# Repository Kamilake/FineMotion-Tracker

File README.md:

# SlimeVR Based Full-Body Tracker

```
혹시 트래커를 어디선가 구해서 QR코드를 스캔해 여기에 왔고 구매자가 아무것도 알려주지 않았다면 디스코드 kamilake 로 디엠주세요!
```

ESP8266 Motion Capture Devices for SlimeVR Ecosystem

Thinnest SlimeVR Tracker!

Full SMT PCB operating in MPU-6500 6DoF mode

Operate with all 5V chargers, including C to C PD chargers.

You can use it simply by ordering it from the fabricator

<!--

-->

## Why should that tracker be able to be detached from the strap?

It is because of the start-up calibration of the MPU-6000 series.

When the MPU first powers up, the DMP measures the static noise, but this needs to be done on every boot. In other words, to reboot the tracker in-game, you must detach it from your body. Not only does this strap adapter help make it very convenient, but it is also a great help in tracker maintenance!

It only takes 10 seconds for you to assemble the tracker sensor and adapter, and less than 30 seconds to assemble all the trackers to your body \:P

It is eco-friendly to save the life of Velcro straps and easily replace broken adapters.

## Specification

- Power Rating: 500mA@5V (TProg: 2.4KOhm)
- Wi-Fi: 802.11bgn 2.4GHz (20.5mW@2dBi)
- Protection Circuit: Depend on battery
- IMU: Invensense MPU-6500 6DoF Attitude detection sensor
- The radio wave safety of this product has been verified by a nationally recognized testing agency.

## Prerequirements

- PCB: [This Repo!](/PCBs)
- 3D Model: [This Repo!](/3D%20Models)
- Belt Strap: https://aliexpress.com/item/1005003002833146.html, or any 50mm width Strap
- Battery: https://aliexpress.com/item/1005004165245143.html, or any 702050 Cell
- USB Cable: https://aliexpress.com/item/1005004409330904.html, or any Type-C cables

## How do I make it?

1. [Order PCB!](/PCBs)
2. Order Belt, Battery!
3. [Print Shell!](/3D%20Models)
4. Go to SteamVR...

## defines.h
```cpp
#define FineMotion_v5
#define IMU IMU_MPU6500
#define IMU_ROTATION DEG_0
#define BOARD BOARD_NODEMCU
#define SECOND_IMU IMU
#define SECOND_IMU_ROTATION IMU_ROTATION
#define BATTERY_MONITOR 1
#define BATTERY_SHIELD_RESISTANCE 0
#define BATTERY_SHIELD_R1 12
#define BATTERY_SHIELD_R2 47
#define PIN_IMU_SDA 4
#define PIN_IMU_SCL 5
#define PIN_IMU_INT 0xFF
#define PIN_IMU_INT_2 0xFF
#define PIN_BATTERY_LEVEL 17
```

## Why do trackers have to be thin?

The thinner the tracker, the closer the IMU is to the bone and the better the tracking accuracy. It is less affected by inertial force in fast movements.. Above all, it is comfortable when lying on the bed facing the tracker!

## License
**This hardware is licensed under the CERN-OHL-P v2 license**, which is a permissive,
non-viral and non-reciprocal open hardware license. Unlike software licenses like
MIT and Apache 2.0, it better handles the nuances of hardware and protects both
the licensor and licensee from patent lawsuits.

**Unless you explicitly state otherwise, any contribution intentionally submitted
for inclusion in this work by you, shall be licensed as above, without any
additional terms or conditions.**

### Conveying notice of License
Note that as part of the CERN-OHL-P v2 license, recipients of manufactured
hardware must also receive notice of the above license. One such
method of conveying the notice is to include a link to the original source repo,
or printing "Licensed under CERN-OHL-P v2" on the PCB silkscreen. For more info,
see [here](https://ohwr.org/project/cernohl/wikis/Documents/CERN-OHL-version-2).

This is conceptually similar to the MIT/Apache 2.0 Licenses, where the original
license must still be included as a notice even when the source is modified and
subsequently relicensed under different terms.

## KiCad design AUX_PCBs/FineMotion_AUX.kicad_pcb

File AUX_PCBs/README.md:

# Custom assembly using Kikit JLC

Due to JLCPCB's new assembly policy, soldering on the bottom side or using a non-black PCB will incur additional charges.
Bottom side soldering is not possible if the "Economic" assembly option is selected.
As the bottom side soldering is only for the connector, manual assembly is recommended.  
But.. if you ordering more than 31 boards, it is more economical to choose the `Standard assembly` option with panelization.  
If you have any further questions, please feel free to contact me!(Issues, mail, Discord, etc.)  

- You need `KiCad 6.0 Command Prompt` and [Kikit](https://github.com/yaqwsx/KiKit) with KiCad 6

## Panalize and Fabrication

```batch
kikit panelize ^
    -p :jlcTooling ^
    --layout "grid; rows: 7; cols: 3; space: 3mm" ^
    --tabs "fixed; hwidth: 10mm; vwidth: 15mm" ^
    --cuts vcuts ^
    --source "tolerance: 1000mm" ^
    --framing "tightframe; width: 5mm; space: 3mm; " ^
    --post "millradius: 1mm" ^
    "./FineMotion_AUX.kicad_pcb" ^
    "FineMotion_AUX_panel.kicad_pcb"

kikit fab jlcpcb ^
    --assembly ^
    --schematic ./FineMotion_AUX.kicad_sch ^
    --ignore TP1,J1 ^
    "./FineMotion_AUX_panel.kicad_pcb" ^
    "./Gerber/FineMotion_Panel"

```

## Fabrication Only

### Using Default Configuration

```batch
kikit fab jlcpcb ^
    --assembly ^
    --schematic ./FineMotion_AUX.kicad_sch ^
    --ignore TP1,TP2 ^
    --no-drc ^
    "./FineMotion_AUX_panel.kicad_pcb" ^
    "./Gerber/FineMotion"
```

<br><hr><br>

## Panalize and Fabrication Extension Sensor

```batch
```

## Fabrication Extension Sensor Only

### Using Default Configuration

```batch
```

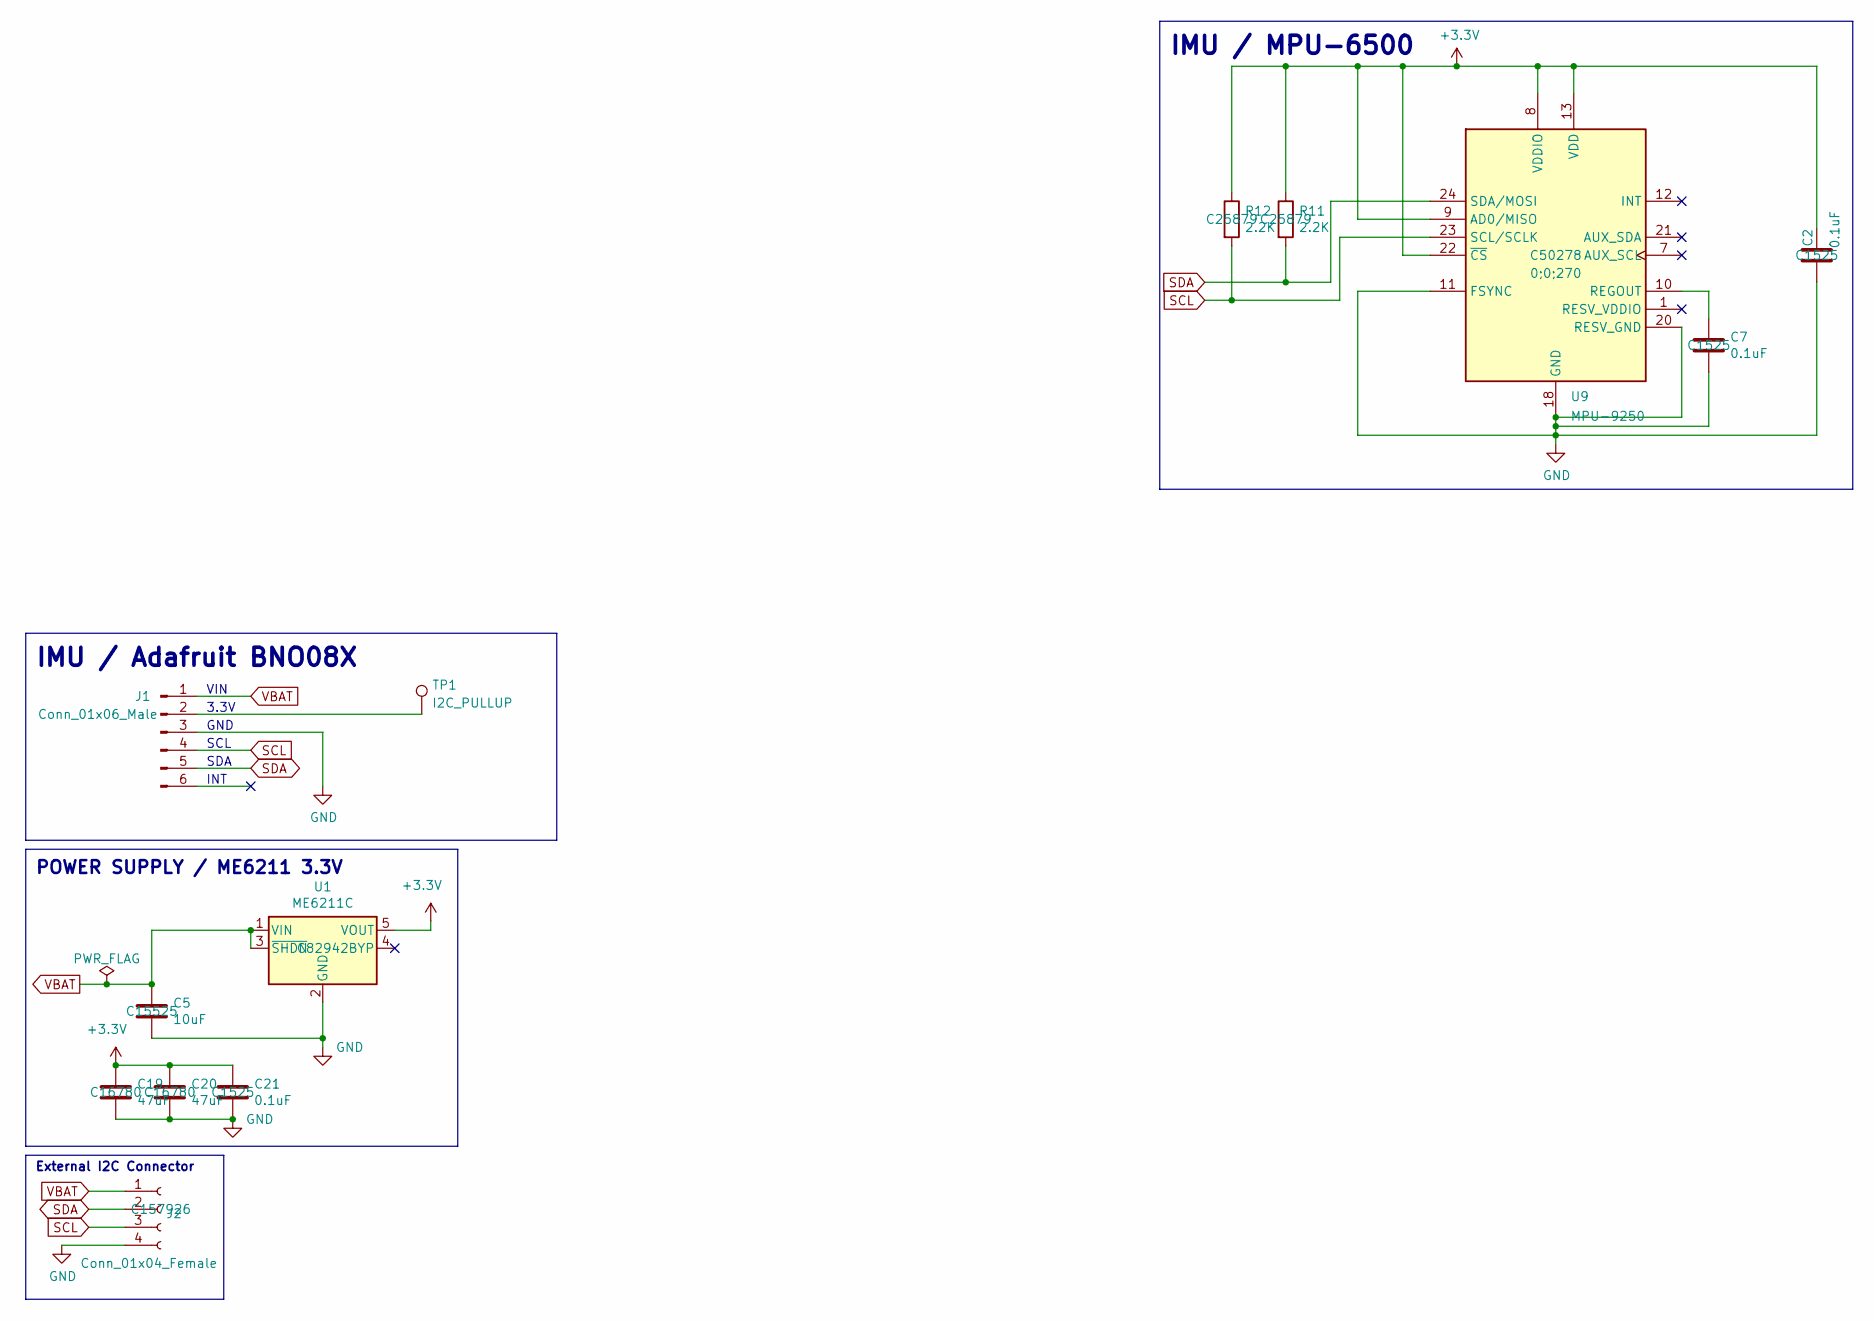
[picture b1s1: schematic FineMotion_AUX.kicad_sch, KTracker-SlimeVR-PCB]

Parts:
C2, C7, C21: 0.1uF; C_0402_1005Metric; LCSC C1525
C5: 10uF; C_0402_1005Metric; LCSC C15525
C19, C20: 47uF; C_0805_2012Metric; LCSC C16780
J1: Conn_01x06_Male; PinHeader_1x06_P2.54mm_Vertical
J2: Conn_01x04_Female; JST_PH_S4B-PH-K_1x04_P2.00mm_Horizontal; LCSC C157926
R11, R12: 2.2K; R_0402_1005Metric; LCSC C25879
TP1: I2C_PULLUP; TestPoint_Pad_D1.5mm
U1: ME6211C; SOT-23-5; LCSC C82942
U9: MPU-9250; InvenSense_QFN-24_3x3mm_P0.4mm; LCSC C50278

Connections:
+3V3: C2.2, C19.1, C20.1, C21.1, R11.1, R12.1, U1.5 (VOUT), U9.8 (VDDIO), U9.9 (AD0/MISO), U9.13 (VDD), U9.22 (~CS)
GND: C2.1, C5.2, C7.2, C19.2, C20.2, C21.2, J1.3, J2.4, U1.2 (GND), U9.11 (FSYNC), U9.18 (GND), U9.20 (RESV_GND)
unnamed: C7.1, U9.10 (REGOUT)
unnamed: J1.2, TP1.1
SCL: J1.4, J2.3, R12.2, U9.23 (SCL/SCLK)
SDA: J1.5, J2.2, R11.2, U9.24 (SDA/MOSI)
VBAT: C5.1, J1.1, J2.1, U1.1 (VIN), U1.3 (~SHDN)

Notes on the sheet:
External I2C Connector
SCL
IMU / MPU-6500
SDA
IMU / Adafruit BNO08X
POWER SUPPLY / ME6211 3.3V
GND
VIN
INT
3.3V

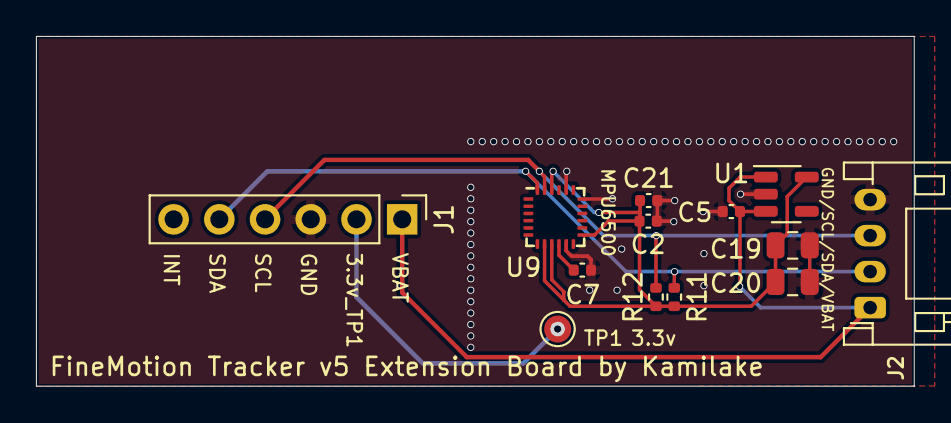
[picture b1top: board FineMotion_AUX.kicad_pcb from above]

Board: 2 copper layers, 48.8 x 19.4 mm, 13 parts (0 on the bottom side), 7 nets.

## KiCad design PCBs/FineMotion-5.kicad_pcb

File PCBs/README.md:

# Custom assembly using Kikit JLC

Due to JLCPCB's new assembly policy, soldering on the bottom side or using a non-black PCB will incur additional charges.   
Bottom side soldering is not possible if the "Economic" assembly option is selected.   
As the bottom side soldering is only for the connector, manual assembly is recommended.  
But.. if you ordering more than 31 boards, it is more economical to choose the `Standard assembly` option with panelization.  
If you have any further questions, please feel free to contact me!(Issues, mail, Discord, etc.)  

- You need `KiCad 6.0 Command Prompt` and [Kikit](https://github.com/yaqwsx/KiKit) with KiCad 6

## Panalize and Fabrication
```batch
kikit panelize ^
    -p :jlcTooling ^
    --layout "grid; rows: 7; cols: 3; space: 3mm" ^
    --tabs "fixed; hwidth: 10mm; vwidth: 15mm" ^
    --cuts vcuts ^
    --source "tolerance: 1000mm" ^
    --post "millradius: 1mm" ^
    "./FineMotion-5.kicad_pcb" ^
    "FineMotion-5_panel.kicad_pcb"

kikit fab jlcpcb ^
    --assembly ^
    --schematic ./FineMotion-5.kicad_sch ^
    --ignore TP1,TP2 ^
    --no-drc ^
    "./FineMotion-5_panel.kicad_pcb" ^
    "./Gerber/FineMotion_Panel"
```

## Fabrication Only

### Using Default Configuration
```batch
kikit fab jlcpcb ^
    --assembly ^
    --schematic ./FineMotion-5.kicad_sch ^
    --ignore TP1,TP2 ^
    --no-drc ^
    "./FineMotion-5_panel.kicad_pcb" ^
    "./Gerber/FineMotion"
```

<br><hr><br>   

## Panalize and Fabrication Extension Sensor
```batch
```

## Fabrication Extension Sensor Only

### Using Default Configuration
```batch
```
<!--
### Using internal MPU-6050+QMC5883L and Left side Lipo
```batch
kikit fab jlcpcb ^
    --assembly ^
    --schematic ./KTracker.kicad_sch ^
    --ignore BT1,J1,J4,J5 ^
    --no-drc ./KTracker.kicad_pcb ^
    "./Gerber/Using internal MPU-6050+QMC5883L and Left side Lipo"
```

### Using GY-521 and bottom Lipo
```batch
kikit fab jlcpcb ^
    --assembly ^
    --schematic ./KTracker.kicad_sch ^
    --ignore U8,U3,R20,R21,C16,C12,C11,R12,R11,BT1,J3,J4,J5 ^
    --no-drc ./KTracker.kicad_pcb ^
    "./Gerber/Using GY-521 and bottom Lipo"

```

### Using GY-521 and 18650
```batch
kikit fab jlcpcb ^
    --assembly ^
    --schematic ./KTracker.kicad_sch ^
    --ignore U8,U3,R20,R21,C16,C12,C11,R12,R11,J1,J3,J4,J5 ^
    --no-drc ./KTracker.kicad_pcb ^
    "./Gerber/Using GY-521 and 18650"

```

kikit fab jlcpcb --assembly --schematic ./FineMotion-5.kicad_sch --ignore TP1,TP2 --no-drc ./FineMotion-5.kicad_pcb "./Gerber/FM6500"

kikit fab jlcpcb --assembly --schematic ./KTracker_AUX.kicad_sch  --ignore A1 --no-drc ./KTracker_AUX.kicad_pcb "./Gerber/FM6500E"

kikit panelize ^
    -p :jlcTooling ^
    --layout "grid; rows: 7; cols: 3; space: 3mm" ^
    --tabs "fixed; hwidth: 10mm; vwidth: 15mm" ^
    --cuts vcuts ^
    --source "tolerance: 1000mm" ^
    --post "millradius: 1mm" ^
    "./FineMotion-5.kicad_pcb" ^
    "FineMotion-5_panel.kicad_pcb"

kikit fab jlcpcb ^
    --assembly ^
    --schematic ./FineMotion-5.kicad_sch ^
    --ignore TP1,TP2 ^
    --no-drc ^
    "./FineMotion-5_panel.kicad_pcb" ^
    "./Gerber/FineMotion_Panel"

---

-->

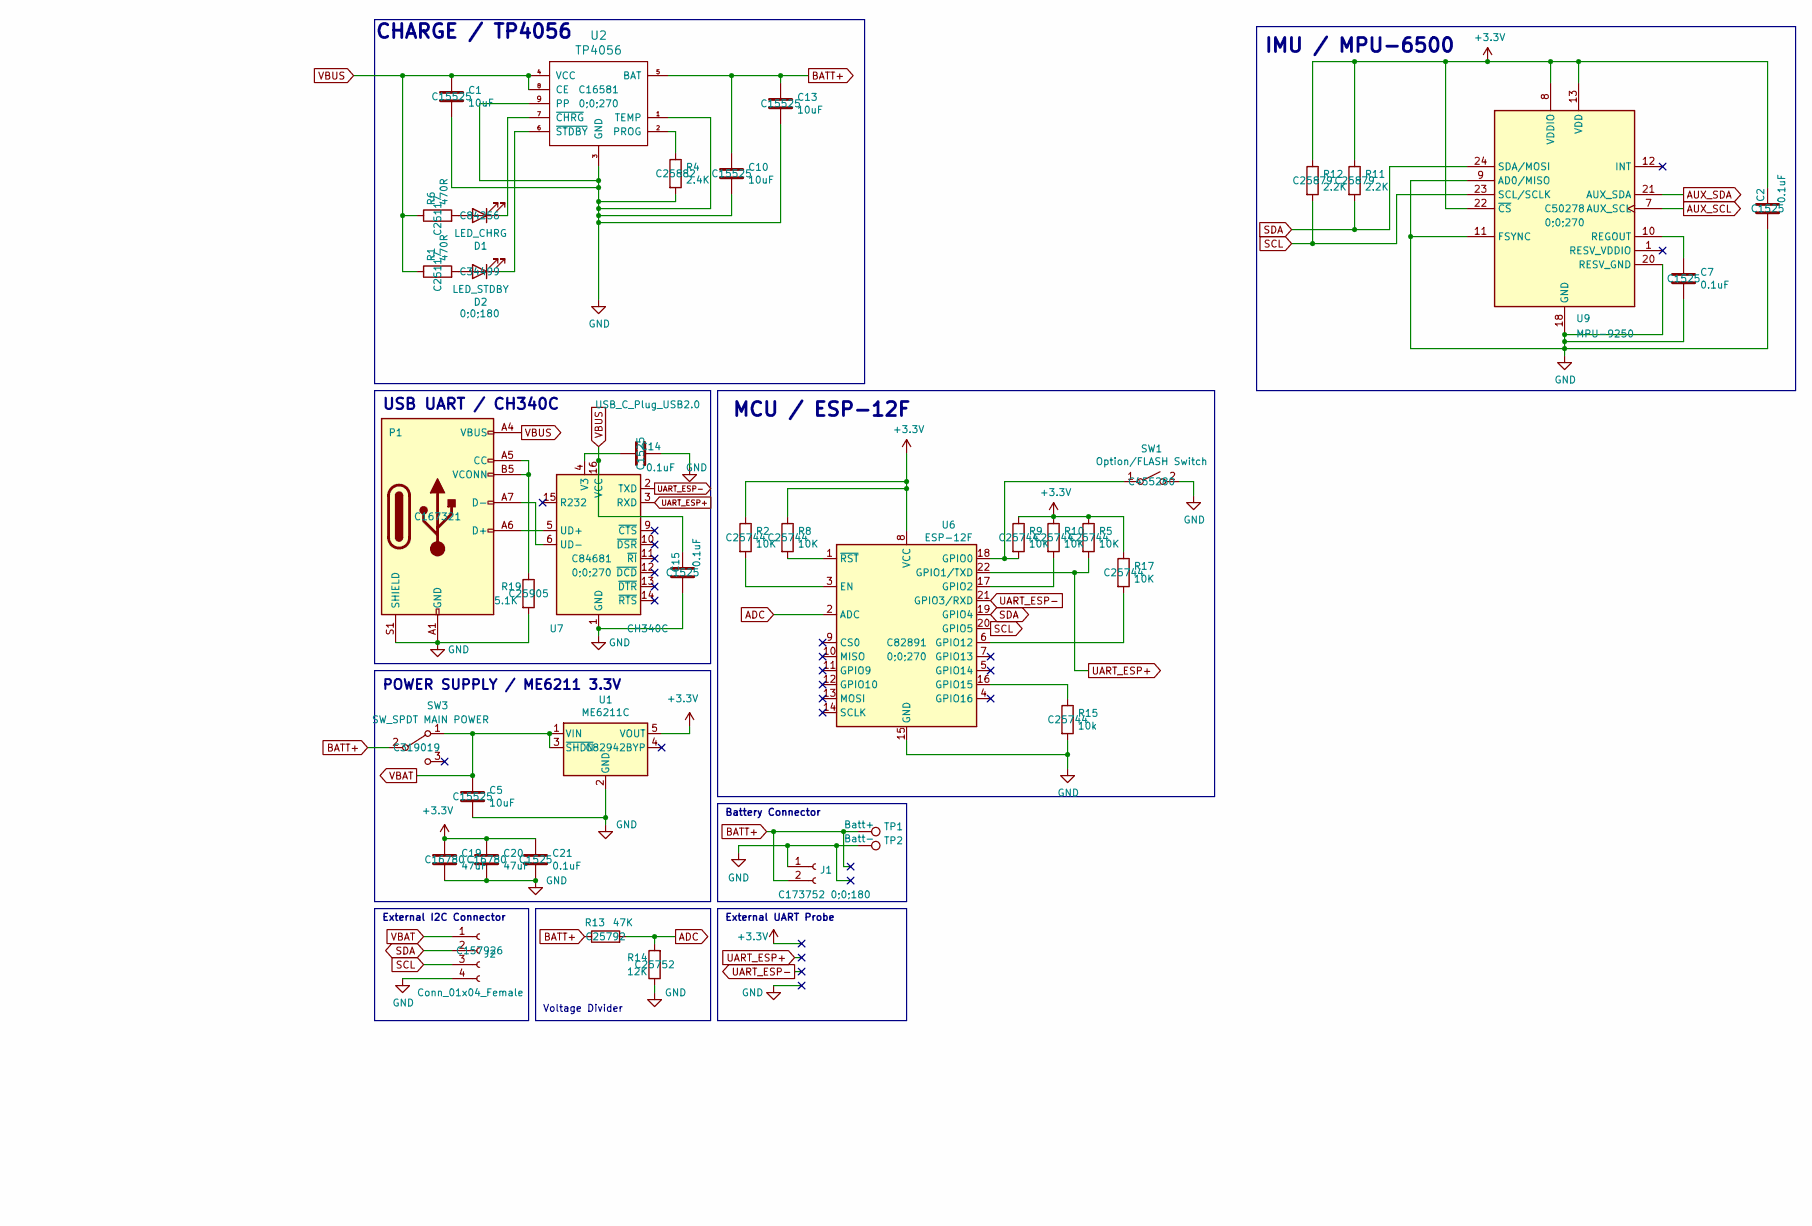
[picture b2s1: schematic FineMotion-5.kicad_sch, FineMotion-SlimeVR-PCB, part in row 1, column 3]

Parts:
C1, C5, C10, C13: 10uF; C_0402_1005Metric; LCSC C15525
C2, C7, C14, C15, C21: 0.1uF; C_0402_1005Metric; LCSC C1525
C19, C20: 47uF; C_0805_2012Metric; LCSC C16780
D1: LED_CHRG; LED_0805_2012Metric; LCSC C84256
D2: LED_STDBY; LED_0805_2012Metric; LCSC C34499
J1: Conn_01x02_Female; JST_PH_S2B-PH-K_1x02_P2.00mm_Horizontal; LCSC C173752
J2: Conn_01x04_Female; JST_PH_S4B-PH-K_1x04_P2.00mm_Horizontal; LCSC C157926
P1: USB_C_Plug_USB2.0; USB_C_Receptacle_HRO_TYPE-C-31-M-12; LCSC C167321
R1, R6: 470R; R_0402_1005Metric; LCSC C25117
R2, R5, R8, R9, R10, R17: 10K; R_0402_1005Metric; LCSC C25744
R4: 2.4K; R_0402_1005Metric; LCSC C25882
R11, R12: 2.2K; R_0402_1005Metric; LCSC C25879
R13: 47K; R_0402_1005Metric; LCSC C25792
R14: 12K; R_0402_1005Metric; LCSC C25752
R15: 10k; R_0402_1005Metric; LCSC C25744
R19: 5.1K; R_0402_1005Metric; LCSC C25905
SW1: Option/FLASH Switch; TS-1088R; LCSC C455280
SW3: SW_SPDT MAIN POWER; SW_SPDT_PCM12; LCSC C319019
TP1: Batt+; Pin_D0.9mm_L10.0mm_W2.4mm_FlatFork
TP2: Batt-; Pin_D0.9mm_L10.0mm_W2.4mm_FlatFork
U1: ME6211C; SOT-23-5; LCSC C82942
U2: TP4056; HSOP-8-1EP_3.9x4.9mm_P1.27mm_EP2.41x3.1mm_ThermalVias; LCSC C16581
U6: ESP-12F; ESP-12E; LCSC C82891
U7: CH340C; SOIC-16_3.9x9.9mm_P1.27mm; LCSC C84681
U9: MPU-9250; InvenSense_QFN-24_3x3mm_P0.4mm; LCSC C50278

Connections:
+3V3: C2.2, C19.1, C20.1, C21.1, R2.1, R5.1, R8.1, R9.1, R10.1, R11.1, R12.1, R17.1, U1.5 (VOUT), U6.8 (VCC), U9.8 (VDDIO), U9.13 (VDD), U9.22 (~CS)
ADC: R13.2, R14.2, U6.2 (ADC)
AUX_SCL: U9.7 (AUX_SCL)
AUX_SDA: U9.21 (AUX_SDA)
BATT+: C10.1, C13.1, J1.2, R13.1, SW3.2 (B), TP1.1, U2.5 (BAT)
GND: C1.2, C2.1, C5.2, C7.2, C10.2, C13.2, C14.2, C15.1, C19.2, C20.2, C21.2, J1.1, J2.4, P1.A1 (GND), P1.A12 (GND), P1.B1 (GND), P1.B12 (GND), P1.S1 (SHIELD), R4.2, R14.1, R15.2, R19.2, SW1.2 (B), TP2.1, U1.2 (GND), U2.1 (TEMP), U2.3 (GND), U2.9 (PP), U6.15 (GND), U7.1 (GND), U9.9 (AD0/MISO), U9.11 (FSYNC), U9.18 (GND), U9.20 (RESV_GND)
unnamed: C7.1, U9.10 (REGOUT)
unnamed: C14.1, U7.4 (V3)
unnamed: D1.1 (K), U2.7 (~CHRG)
unnamed: D1.2 (A), R6.2
unnamed: D2.1 (K), U2.6 (~STDBY)
unnamed: D2.2 (A), R1.2
unnamed: P1.A5 (CC), P1.B5 (VCONN), R19.1
unnamed: P1.A6 (D+), U7.5 (UD+)
unnamed: P1.A7 (D-), U7.6 (UD-)
unnamed: R2.2, U6.3 (EN)
unnamed: R4.1, U2.2 (PROG)
unnamed: R8.2, U6.1 (~RST)
unnamed: R9.2, SW1.1 (A), U6.18 (GPIO0)
unnamed: R10.2, U6.17 (GPIO2)
unnamed: R15.1, U6.16 (GPIO15)
unnamed: R17.2, U6.6 (GPIO12)
SCL: J2.3, R12.2, U6.20 (GPIO5), U9.23 (SCL/SCLK)
SDA: J2.2, R11.2, U6.19 (GPIO4), U9.24 (SDA/MOSI)
UART_ESP+: R5.2, U6.22 (GPIO1/TXD), U7.3 (RXD)
UART_ESP-: U6.21 (GPIO3/RXD), U7.2 (TXD)
VBAT: C5.1, J2.1, SW3.1 (A), U1.1 (VIN), U1.3 (~SHDN)
VBUS: C1.1, C15.2, P1.A4 (VBUS), P1.A9 (VBUS), P1.B4 (VBUS), P1.B9 (VBUS), R1.1, R6.1, U2.4 (VCC), U2.8 (CE), U7.16 (VCC)

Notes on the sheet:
Voltage Divider
External UART Probe
MCU / ESP-12F
External I2C Connector
IMU / MPU-6500
POWER SUPPLY / ME6211 3.3V
CHARGE / TP4056
USB UART / CH340C
Battery Connector

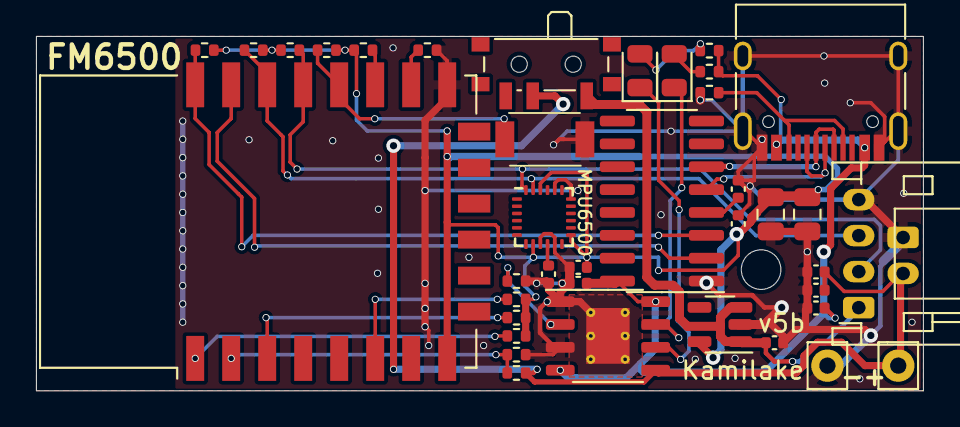
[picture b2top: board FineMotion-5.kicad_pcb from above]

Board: 2 copper layers, 49.3 x 19.7 mm, 40 parts (1 on the bottom side), 26 nets.

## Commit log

2022-12-02 FineMotion!
2022-12-17 Update PCB Remark
2022-12-17 Update gitignore
2022-12-24 ignore panel
2023-02-01 renamed: KTracker_Extension v5a.wrl -> FimeMotion AUX Sensor PCB 3D Model v5a.wrl
2023-02-01 renamed: AUX_PCBs/KTracker_AUX.kicad_pcb -> AUX_PCBs/FineMotion_AUX.kicad_pcb
2023-02-01 Update 3D Model to v172
2023-02-01 File List
2023-02-06 Fix incorrect objects
2023-02-08 Placement of pads to assemble the BNO085 module
2023-02-08 Premium logo~
2023-02-15 Respond to new JLCPCB regulations.
2023-02-15 Update manufacturing date
2023-02-15 Ignore backup

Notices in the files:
AUX_PCBs/FineMotion_AUX.kicad_sch:
Licensed under CERN-OHL-P v2 or later
